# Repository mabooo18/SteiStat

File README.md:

# SteiStat – A Simple and Low-Cost Potentiostat with EIS Capability

This repository contains the open-source hardware and software of the **SteiStat** potentiostat described in the manuscript  
*SteiStat – a Simple and Low-Cost Potentiostat with Electrochemical Impedance Spectroscopy Capability*  
(Analytical Methods, Royal Society of Chemistry, 2025)

---

## About SteiStat
**SteiStat** is a low-cost (30 USD), open-source potentiostat capable of performing  
- **cyclic voltammetry (CV)**,
- **open-circuit potential (OCP)** measurements,
- **electrochemical impedance spectroscopy (EIS)**.  

The instrument is based on the **AD5941** analog front-end and a **Seeeduino XIAO RP2040** microcontroller, which together enable accurate DC and AC electrochemical techniques.  
The system supports EIS at the measured OCP potential and includes free, standalone Windows software for data acquisition and visualization.  

SteiStat is designed for **analytical chemistry, electrochemical research, and education**, allowing researchers and students to perform reliable electrochemical experiments at minimal cost.

---

## Repository Structure

- **Hardware**: This folder contains the files required for ordering the printed circuit board.
- **Samples**: CV and EIS measurement diagrams of different samples measured with SteiStat.
- **Software**: Arduino and GUI software components of SteiStat.
- **supplementary**: Supporting document of the project.

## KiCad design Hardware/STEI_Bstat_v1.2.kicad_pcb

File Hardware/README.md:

This folder contains the full KiCad hardware design source for the Steistat
potentiostat carrier board (`STEI_Bstat_v1.2`), consolidated from a previous
separate export folder.

- `STEI_Bstat_v1.2.kicad_sch` / `.kicad_pcb` / `.kicad_pro` / `.kicad_prl` /
  `.kicad_dru` / `.net` — the KiCad project itself (schematic, PCB layout,
  project settings, design rules, netlist). Open `STEI_Bstat_v1.2.kicad_pro`
  in KiCad to edit.
- `Production/bom-1.csv` and `Production/positions.csv` — the current,
  machine-generated Bill of Materials and pick-and-place file, exported
  directly from the PCB above. This is the BOM used in the project's
  Elsevier/HardwareX manuscript (`journal/paper4/`).
- `Production/STEI_Bstat_v1.2.zip` — a fabrication-ready export bundle.
- `Gerber_PCB.zip` — Gerber/drill files for ordering the bare PCB from any
  manufacturer.
- `Schematic_AD5941 corr. circ. diag._2025-12-14.pdf` — a rendered PDF of
  the schematic, for reference without opening KiCad.
- `DFM analysis report_JLCDFM_STEI_Bstat_v1.2.pdf` — a design-for-manufacture
  check report.
- `Connector_PinHeader_2.54mm_NoGND.pretty/`, `fp-lib-table`,
  `fabrication-toolkit-options.json` — supporting KiCad footprint library
  and fabrication-toolkit plugin files the project depends on.

Using the Gerbers together with the BOM and pick-and-place files, the board
can be ordered as a fully assembled and pre-soldered unit from most PCB
manufacturing services (see `journal/paper4/sections/6-build-instructions.tex`
for the full build procedure).

## `legacy/`

Older exported files kept for reference, superseded by the files above:

- `HunSta2_BOM_corr_OUTDATED.xlsx` — an earlier Bill of Materials export
  whose component values **do not match** the current schematic/PCB (e.g.
  it predates the `RCAL1`/`RCAL2`/`RCAL3` calibration-resistor bank and the
  Randles-branch values used throughout the paper). Use `Production/bom-1.csv`
  instead.
- `SteiStat_CPL.xlsx` — an earlier pick-and-place export in spreadsheet
  form; superseded by `Production/positions.csv`.

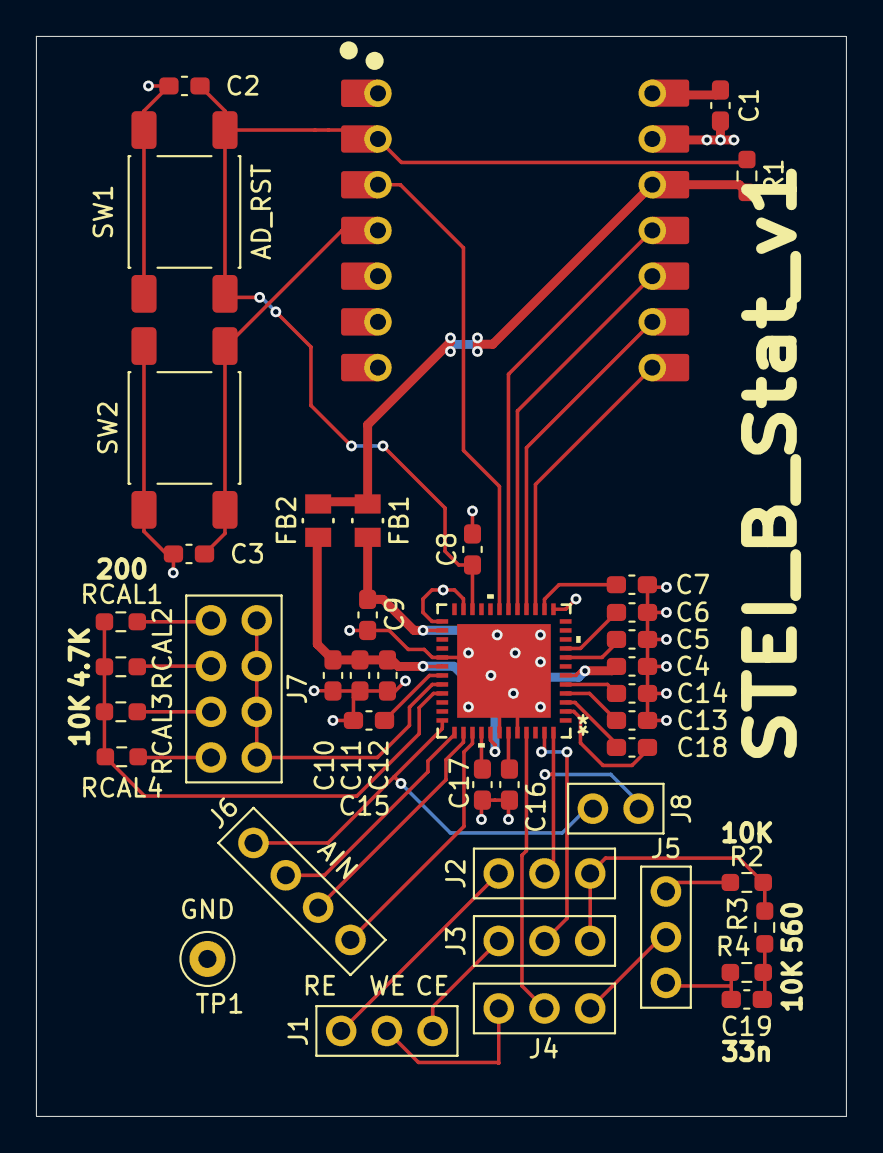
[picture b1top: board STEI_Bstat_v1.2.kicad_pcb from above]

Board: 2 copper layers, 45.0 x 60.0 mm, 42 parts (0 on the bottom side), 43 nets.

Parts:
C1, C2, C3, C4, C5, C6, C8, C9, C10, C12, C17: 100n; C_0603_1608Metric_Pad1.08x0.95mm_HandSolder
C7, C13, C14, C15: 470n; C_0603_1608Metric_Pad1.08x0.95mm_HandSolder
C11: 10u; C_0603_1608Metric_Pad1.08x0.95mm_HandSolder
C16: 4,7u; C_0603_1608Metric_Pad1.08x0.95mm_HandSolder
C18: 220p; C_0603_1608Metric_Pad1.08x0.95mm_HandSolder
C19: 33n; C_0603_1608Metric_Pad1.08x0.95mm_HandSolder
FB1, FB2: FerriteBead; IND_BLM21_MUR
J1, J2, J3, J4, J5: Conn_01x03; PinHeader_1x03_P2.54mm_Vertical_NoGND
J6: Conn_01x04; PinHeader_1x04_P2.54mm_Vertical_NoGND
J7: Conn_02x04_Odd_Even; PinHeader_2x04_P2.54mm_Vertical_NoGND
J8: Conn_01x02; PinHeader_1x02_P2.54mm_Vertical_NoGND
R1, R2, R4: 10K; R_0603_1608Metric_Pad0.98x0.95mm_HandSolder
R3: 560; R_0603_1608Metric_Pad0.98x0.95mm_HandSolder
RCAL1: 200; R_0603_1608Metric_Pad0.98x0.95mm_HandSolder
RCAL2: 4.7K; R_0603_1608Metric_Pad0.98x0.95mm_HandSolder
RCAL3: 10K; R_0603_1608Metric_Pad0.98x0.95mm_HandSolder
RCAL4: R_0603_1608Metric_Pad0.98x0.95mm_HandSolder
SW1, SW2: SW_Push_Dual; SW_Push_1P1T_NO_E-Switch_TL3301NxxxxxG
TP1: TestPoint; TestPoint_Loop_D2.50mm_Drill1.0mm
U1: AD5941BCPZ; CP-48-4_ADI-L
U2: XIAO-RP2040-DIP

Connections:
3V3: FB1.2, FB2.1, R1.1, U2.12 (3V3)
AGND: C1.2, C2.2, C3.2, C4.2, C5.1, C6.1, C7.1, C8.1, C9.1, C10.2, C11.2, C12.2, C13.2, C14.2, C15.2, C16.2, C17.2, SW1.2, SW2.2, TP1.1 (1_1), U1.13 (DGND), U1.23 (DGND), U1.25 (DGND), U1.29 (AGND), U1.42 (AGND), U1.44 (AGND_REF), U1.49 (GND), U2.13 (GND)
AIN0: J6.1, U1.39 (AIN0)
AIN1: J6.2, U1.38 (AIN1)
AIN2: J6.3, U1.37 (AIN2)
AIN3: J6.4, J8.2, U1.36 (AIN3/BUF_VREF1V8)
AIN4/LPF0: C17.1, U1.40 (AIN4/LPF0)
AVDD: C10.1, C11.1, C12.1, FB2.2, U1.30 (AVDD), U1.41 (AVDD)
AVDD_REG: C14.1, U1.5 (AVDD_REG)
CE: J3.2, U1.47 (CE0)
CE_Dummy: J2.3, J3.3, R2.2, R3.2
CE_Pin: J1.3, J3.1
CS: U1.15 (CS), U2.8 (P1_D7_RX)
D3: C3.1, SW2.1, U2.4 (P29_A3_D3)
DVDD: C4.1, C9.2, FB1.1, U1.6 (DVDD), U1.26 (IOVDD)
DVDD_REG_AV8: C7.2, U1.14 (DVDD_REG_AV8)
GPIO0: U1.19 (GPIO0), U2.3 (P28_A2_D2)
MISO: U1.18 (MISO), U2.11 (P3_D10_MISO)
MOSI: U1.17 (MOSI), U2.10 (P4_D9_MOSI)
unnamed: C19.2, R3.1, R4.2
unnamed: J7.1, RCAL1.1
unnamed: J7.3, RCAL2.1
unnamed: J7.5, RCAL3.1
unnamed: J7.7, RCAL4.1
unnamed: C18.1, U1.3 (RC0_0)
unnamed: C18.2, U1.2 (RC0_1)
unnamed: C1.1, U2.14 (VBUS)
RCAL0(32): J7.2, J7.4, J7.6, J7.8, U1.32 (RCAL0)
RCAL1(33): RCAL1.2, RCAL2.2, RCAL3.2, RCAL4.2, U1.33 (RCAL1)
RE: J2.2, J8.1, U1.48 (RE0)
RESET: C2.1, C8.2, R1.2, SW1.1, U1.22 (RESET), U2.2 (P27_A1_D1)
RE_Pin: J1.1, J2.1
SCLK: U1.16 (SCLK), U2.9 (P2_D8_SCK)
VBIAS0: C5.2, U1.8 (VBIAS0)
VBIAS_CAP: C15.1, U1.31 (VBIAS_CAP)
VREF_1V8: C16.1, U1.43 (VREF_1V8)
VREF_2V5: C13.1, U1.4 (VREF_2V5)
VZERO0: C6.2, U1.9 (VZERO0)
WE: J4.2, U1.45 (SE0)
WE_Dummy: J4.3, J5.2
WE_Dummy1: J5.1, R2.1
WE_Dummy2: C19.1, J5.3, R4.1
WE_Pin: J1.2, J4.1

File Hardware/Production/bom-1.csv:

Comment,Designator,Footprint,LCSC
100n,"C1,C10,C12,C17,C2,C3,C4,C5,C6,C8,C9",C_0603_1608Metric_Pad1.08x0.95mm_HandSolder,C14663
10u,C11,C_0603_1608Metric_Pad1.08x0.95mm_HandSolder,C70225
470n,"C13,C14,C15,C7",C_0603_1608Metric_Pad1.08x0.95mm_HandSolder,C1623
4.7u,C16,C_0603_1608Metric_Pad1.08x0.95mm_HandSolder,C19666
220p,C18,C_0603_1608Metric_Pad1.08x0.95mm_HandSolder,C1603
33n,C19,C_0603_1608Metric_Pad1.08x0.95mm_HandSolder,C1614
FerriteBead,"FB1,FB2",L_0805_2012Metric_Pad1.05x1.20mm_HandSolder,C88990
10K,"R1,R2,R4,RCAL3",R_0603_1608Metric_Pad0.98x0.95mm_HandSolder,C25804
560,R3,R_0603_1608Metric_Pad0.98x0.95mm_HandSolder,C23204
200,RCAL1,R_0603_1608Metric_Pad0.98x0.95mm_HandSolder,C8218
4.7K,RCAL2,R_0603_1608Metric_Pad0.98x0.95mm_HandSolder,C23162
TestPoint,TP1,TestPoint_Loop_D2.54mm_Drill1.5mm_Beaded,C5199801
AD5941BCPZ,U1,CP-48-4_ADI-L,C650309
XIAO-RP2040-DIP,U2,XIAO-RP2040-DIP,C9900177322
